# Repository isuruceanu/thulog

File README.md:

thulog
======

Description: Temperature &amp; Humidity Usb Logger device based on DHT22 and attiny2313 mcu

Repository Contents
========
* /docs - usefull documents related to attiny2313, dht22
* /src -  code folder
	- /firmare - attiny2313 firmware c code
	- /server  - server side consumer
* /hardware - Kicad project for pcb	

License Information
========

License is [beerware](http://en.wikipedia.org/wiki/Beerware). Distributed as-is; no warranty is given.

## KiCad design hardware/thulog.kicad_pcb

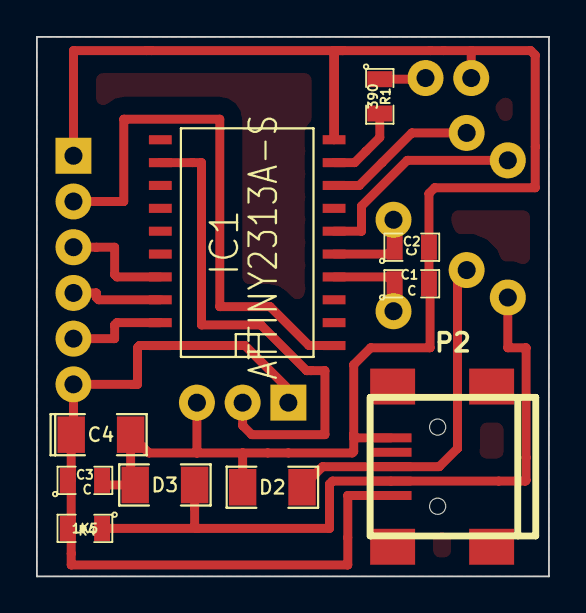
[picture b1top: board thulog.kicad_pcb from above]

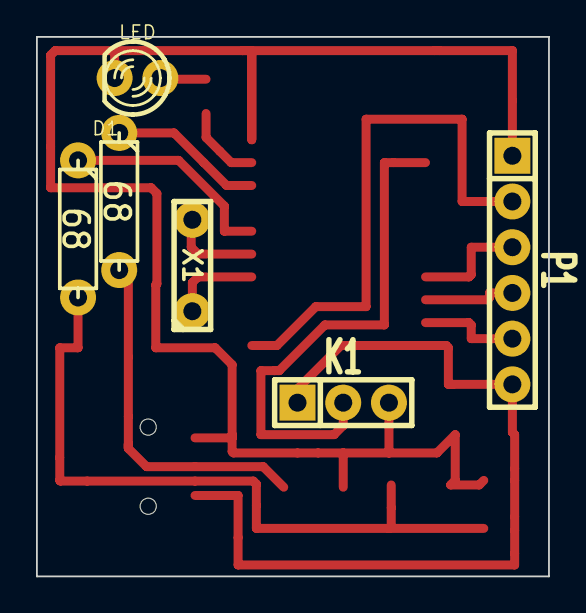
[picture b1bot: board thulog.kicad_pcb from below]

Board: 2 copper layers, 28.4 x 30.0 mm, 16 parts (6 on the bottom side), 15 nets.

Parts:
C1, C2, C3: C; SM0805
C4: CP1; SM1206POL
D1: LED; LED-3MM
D2, D3: ZENER; SM1206
IC1: ATTINY2313A-S; SO20L
K1: DHT; SIL-3
P1: ISP; SIL-6
P2: USBmini; USB_MINI_B
R1: 390; SM0805
R2, R3: 68; R3
R4: 1K5; SM0805
X1: QUARTZCMS4; C2

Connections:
GND: C1.2, C2.2, C3.2, C4.2, D1.2, D2.1, D3.1, IC1.10, K1.3, P1.1, P2.5
unnamed: IC1.12, K1.2
unnamed: IC1.19, P1.5
unnamed: IC1.18, P1.4
unnamed: IC1.17, P1.3
unnamed: IC1.9, R1.2
unnamed: D1.1, R1.1
unnamed: IC1.8, R3.1
unnamed: C1.1, IC1.4, X1.1
unnamed: C2.1, IC1.5, X1.3
unnamed: IC1.6, R2.1
unnamed: D3.2, P2.2, R2.2, R4.1
unnamed: D2.2, P2.3, R3.2
RESET: IC1.1, P1.2
VCC: C3.1, C4.1, IC1.20, K1.1, P1.6, P2.1, R4.2

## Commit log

2014-06-17 Added initial project structure and some usefull docs
2014-06-17 added firmware main file
2014-06-17 added makefile
2014-06-17 first compilation, added usblibs
2014-06-17 added git ignore file
2014-06-17 trying to setup watchdog and sleep mode
2014-06-18 test markdown
2014-06-18 Update README.md
    testing
2014-06-18 added todo.md file
2014-06-18 moved todo list to readme and removed todo.md file
2014-06-18 updated todo list
2014-06-18 renamed usb device name and vendor
2014-06-18 Added first implementation of sensor reading lib
2014-06-18 1. renamed dth to dht, 2. included dht into main program and compiled
2014-06-18 added missed file
2014-06-18 start working on sending data to consummer
2014-06-19 refactored the code in order to fit into 2kb
2014-06-23 made mcu to sleep and wake up every 4 seconds to blink the led, commented dht functionality
2014-06-23 included dht functinality back
2014-06-24 read data, started working on test console
2014-06-24 added test console app
2014-06-24 made console to build
2014-06-24 made console to build on windows, reader is returning 1, start to debug
2014-06-25 can read device but dht11 work pretty stable dht22 pretty unstable
2014-06-25 try to reset mcu if hangsup
2014-06-25 1. changed watchdog for a 1s, read pretty constant , fixed usb vendor and device name
2014-06-25 fixed issue with reading temp, now data are read pretty good everytime
2014-06-25 start working on c# exemple
2014-06-25 forced to add dll file
2014-06-25 added c# solution not working yet
2014-06-25 update ignore list
    added c# ignores
2014-06-25 removed bin and obj
2014-06-25 clean sln
2014-06-27 added kicad project
2014-06-27 removed unused file
2014-06-27 removed bak file, added it to ignore list
2014-06-27 modified quartz
2014-06-27 sync
2014-07-01 drawing the pcb
2014-07-03 finished with pcb, ready to be printed
2014-07-03 adjusted the pbc
2014-07-03 adjusted 0.1uF cap
2014-07-03 finished with pbc, printed
2014-07-08 fixed the d+ to VCC instead of GND, added usb mini-b instead of simple connection pads, minimized the pcb
2014-07-08 small changes in pcb
2014-07-14 updated schema and code cumatch existing pcb
2014-07-20 fixed bug in pcb d+ pullup resistor to VCC instead of d-. Now the usb is recognised
2014-07-28 investigate HID usb type, first branch commit
2014-08-05 Clean the code in order to test HID
2014-08-29 Finaly was able to send command to device from .net
2014-08-29 reverted the thulog code to read temp and hum. works fine from .net know
2014-08-29 Added .net infrastructure
2014-08-29 removed old c# project, moving it to dot.net folder
2014-08-29 added thulog.net sln with test console application
2014-10-10 changed the usb to be an ordinary usb based un libusb32. Now the device does not read the temerature in c# and c its returns zero. ledon/off is working properly in c# and c
2014-10-17 added Nancy self host
2014-10-24 sleep mode bug fixed
2014-10-28 Added support for storing thulog data to sqlite db file
2014-10-30 can save data to sqlite
2014-10-30 changed repository to be commited
2014-12-23 Thulog service update
2014-12-24 added nuget.exe
